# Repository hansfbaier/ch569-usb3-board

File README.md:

# CH569 USB3 Super Speed Board
USB3 super speed development board useful as FPGA expansion
based on the WCH-Tech CH569 chip.
It should also be possible to substitute the CH569 with a CH565 chip,
without further modifications.

### Board support
Open source development tools and board support package are available here:

https://github.com/orgs/hydrausb3/repositories

### Status
* rev0 tested and working
* rev1 tested and working
* rev2 tested and working. Passes stress test. Recommended!

NOTE: Both rev0 and rev1 have shown spurious transmission errors in USB3 stress tests.
Do not use for high performance duty. Adding a 100nF decoupling capacitor to the
3V3 pin of the crystal oscillator seemed to improve the situation significantly.

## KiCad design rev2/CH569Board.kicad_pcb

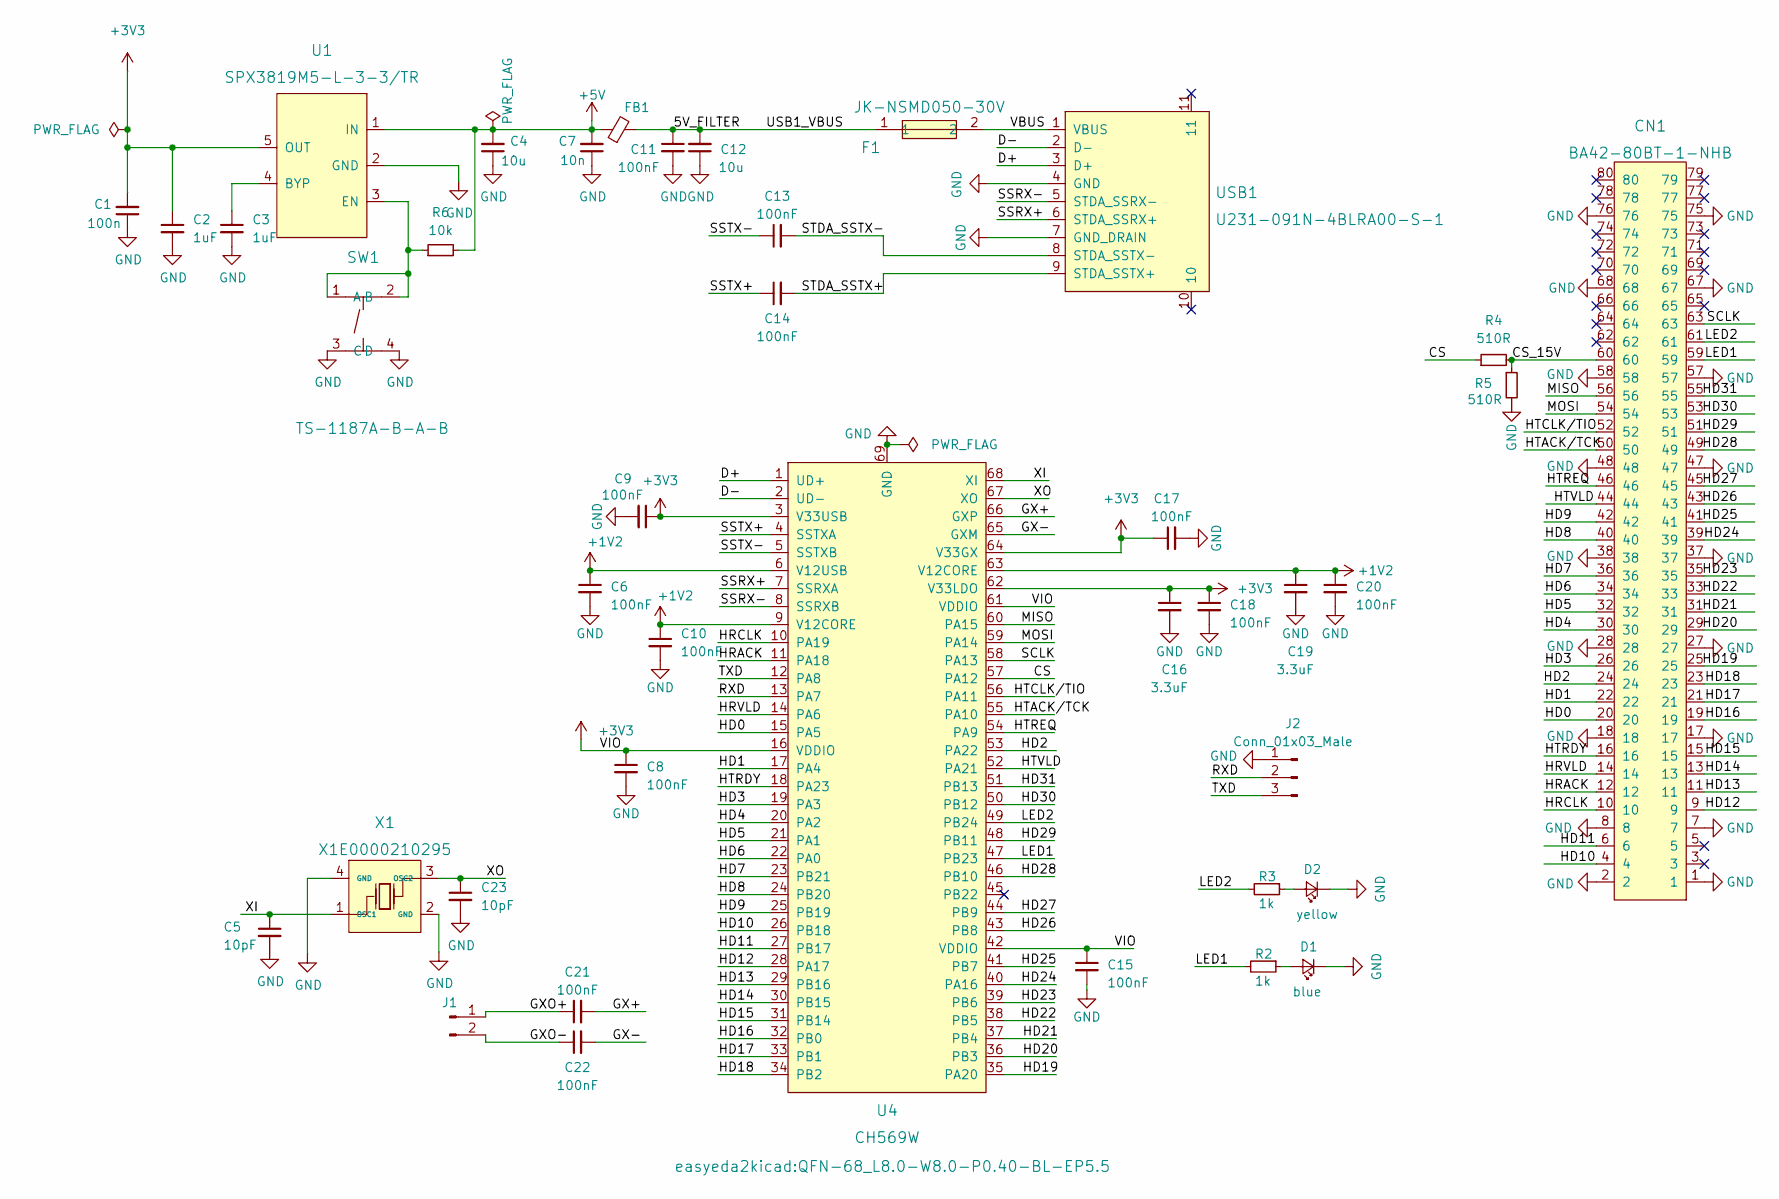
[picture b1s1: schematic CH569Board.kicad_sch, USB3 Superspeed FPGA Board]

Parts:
C1: 100n; C_0805_2012Metric; LCSC C49678
C2, C3: 1uF; C_0805_2012Metric; LCSC C28323
C4, C12: 10u; C_0805_2012Metric; LCSC C15850
C5, C23: 10pF; C_0402_1005Metric; LCSC C32949
C6, C8, C9, C10, C11, C17, C18, C20: 100nF; C_0805_2012Metric; LCSC C49678
C7: 10n; C_0805_2012Metric; LCSC C1710
C13, C14, C21, C22: 100nF; C_0402_1005Metric; LCSC C1525
C15: 100nF; C_0603_1608Metric; LCSC C14663
C16, C19: 3.3uF; C_0603_1608Metric; LCSC C51412
CN1: BA42-80BT-1-NHB; CONN-SMD_BA42-80BT-1-NHB; LCSC Part C508676
D1: blue; LED_0603_1608Metric; LCSC C72041
D2: yellow; LED_0603_1608Metric; LCSC C72038
F1: JK-NSMD050-30V; F1206; LCSC Part C720075
FB1: 2A; L_1206_3216Metric; LCSC C73732
J1: Conn_01x02_Male; PinHeader_1x02_P2.54mm_Vertical
J2: Conn_01x03_Male; PinHeader_1x03_P2.54mm_Vertical
R2, R3: 1k; R_0603_1608Metric; LCSC C21190
R4, R5: 510R; R_0402_1005Metric; LCSC C25123
R6: 10k; R_0402_1005Metric; LCSC C25744
SW1: TS-1187A-B-A-B; SW-SMD_4P-L5.1-W5.1-P3.70-LS6.5-TL-2; LCSC Part C318884
U1: SPX3819M5-L-3-3/TR; SOT-23-5_L3.0-W1.7-P0.95-LS2.8-BR; LCSC Part C9055
U4: CH569W; QFN-68_L8.0-W8.0-P0.40-BL-EP5.5; LCSC Part C2857462
USB1: U231-091N-4BLRA00-S-1; USB-A-SMD_U231-091N-4BLRA00-S-1; LCSC Part C381140
X1: X1E0000210295; CRYSTAL-SMD_4P-L3.2-W2.5-BL; LCSC Part C255930

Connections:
+1V2: C6.1, C10.1, C19.1, C20.1, U4.6 (V12USB), U4.9 (V12CORE), U4.63 (V12CORE)
+3V3: C1.2, C2.1, C8.1, C9.1, C15.1, C16.1, C17.1, C18.1, U1.5 (OUT), U4.3 (V33USB), U4.16 (VDDIO), U4.42 (VDDIO), U4.61 (VDDIO), U4.62 (V33LDO), U4.64 (V33GX)
+5V: C4.2, C7.2, FB1.1, R6.2, U1.1 (IN)
/5V_FILTER: C11.1, C12.2, F1.1, FB1.2
/CS: R4.1, U4.57 (PA12)
/CS_15V: CN1.60, R4.2, R5.1
/D+: U4.1 (UD+), USB1.3 (D+)
/D-: U4.2 (UD-), USB1.2 (D-)
/GX+: C21.2, U4.66 (GXP)
/GX-: C22.2, U4.65 (GXM)
/GXO+: C21.1, J1.1
/GXO-: C22.1, J1.2
/HD0: CN1.20, U4.15 (PA5)
/HD1: CN1.22, U4.17 (PA4)
/HD2: CN1.24, U4.53 (PA22)
/HD3: CN1.26, U4.19 (PA3)
/HD4: CN1.30, U4.20 (PA2)
/HD5: CN1.32, U4.21 (PA1)
/HD6: CN1.34, U4.22 (PA0)
/HD7: CN1.36, U4.23 (PB21)
/HD8: CN1.40, U4.24 (PB20)
/HD9: CN1.42, U4.25 (PB19)
/HD10: CN1.4, U4.26 (PB18)
/HD11: CN1.6, U4.27 (PB17)
/HD12: CN1.9, U4.28 (PA17)
/HD13: CN1.11, U4.29 (PB16)
/HD14: CN1.13, U4.30 (PB15)
/HD15: CN1.15, U4.31 (PB14)
/HD16: CN1.19, U4.32 (PB0)
/HD17: CN1.21, U4.33 (PB1)
/HD18: CN1.23, U4.34 (PB2)
/HD19: CN1.25, U4.35 (PA20)
/HD20: CN1.29, U4.36 (PB3)
/HD21: CN1.31, U4.37 (PB4)
/HD22: CN1.33, U4.38 (PB5)
/HD23: CN1.35, U4.39 (PB6)
/HD24: CN1.39, U4.40 (PA16)
/HD25: CN1.41, U4.41 (PB7)
/HD26: CN1.43, U4.43 (PB8)
/HD27: CN1.45, U4.44 (PB9)
/HD28: CN1.49, U4.46 (PB10)
/HD29: CN1.51, U4.48 (PB11)
/HD30: CN1.53, U4.50 (PB12)
/HD31: CN1.55, U4.51 (PB13)
/HRACK: CN1.12, U4.11 (PA18)
/HRCLK: CN1.10, U4.10 (PA19)
/HRVLD: CN1.14, U4.14 (PA6)
/HTACK/TCK: CN1.50, U4.55 (PA10)
/HTCLK/TIO: CN1.52, U4.56 (PA11)
/HTRDY: CN1.16, U4.18 (PA23)
/HTREQ: CN1.46, U4.54 (PA9)
/HTVLD: CN1.44, U4.52 (PA21)
/LED1: CN1.59, R2.2, U4.47 (PB23)
/LED2: CN1.61, R3.2, U4.49 (PB24)
/MISO: CN1.56, U4.60 (PA15)
/MOSI: CN1.54, U4.59 (PA14)
/RXD: J2.2, U4.13 (PA7)
/SCLK: CN1.63, U4.58 (PA13)
/SSRX+: U4.7 (SSRXA), USB1.6 (STDA_SSRX+)
/SSRX-: U4.8 (SSRXB), USB1.5 (STDA_SSRX-)
/SSTX+: C14.1, U4.4 (SSTXA)
/SSTX-: C13.1, U4.5 (SSTXB)
/STDA_SSTX+: C14.2, USB1.9 (STDA_SSTX+)
/STDA_SSTX-: C13.2, USB1.8 (STDA_SSTX-)
/TXD: J2.3, U4.12 (PA8)
/VBUS: F1.2, USB1.1 (VBUS)
/XI: C5.1, U4.68 (XI), X1.1 (OSC1)
/XO: C23.1, U4.67 (XO), X1.3 (OSC2)
GND: C1.1, C2.2, C3.2, C4.1, C5.2, C6.2, C7.1, C8.2, C9.2, C10.2, C11.2, C12.1, C15.2, C16.2, C17.2, C18.2, C19.2, C20.2, C23.2, CN1.1, CN1.2, CN1.7, CN1.8, CN1.17, CN1.18, CN1.27, CN1.28, CN1.37, CN1.38, CN1.47, CN1.48, CN1.57, CN1.58, CN1.67, CN1.68, CN1.75, CN1.76, D1.1 (K), D2.1 (K), J2.1, R5.2, SW1.3 (C), SW1.4 (D), U1.2 (GND), U4.69 (GND), USB1.4 (GND), USB1.7 (GND_DRAIN), X1.2 (GND), X1.4 (GND)
unnamed: C3.1, U1.4 (BYP)
unnamed: D1.2 (A), R2.1
unnamed: D2.2 (A), R3.1
unnamed: R6.1, SW1.1 (A), SW1.2 (B), U1.3 (EN)

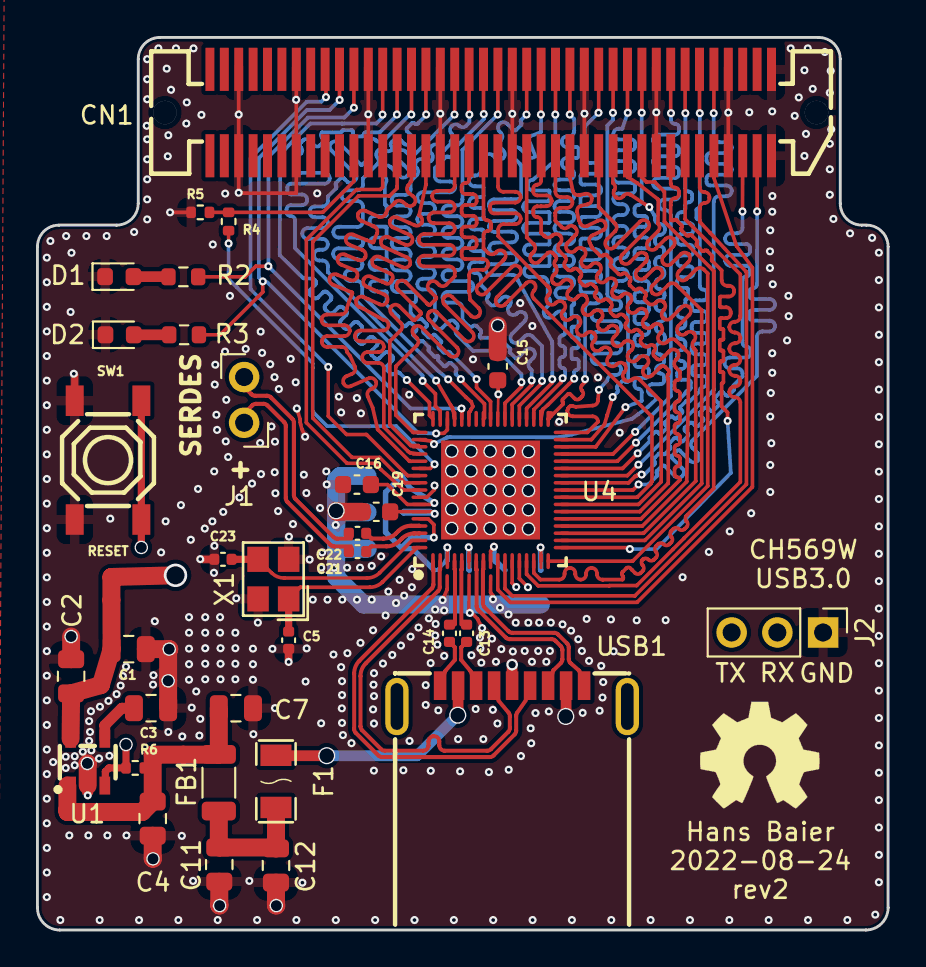
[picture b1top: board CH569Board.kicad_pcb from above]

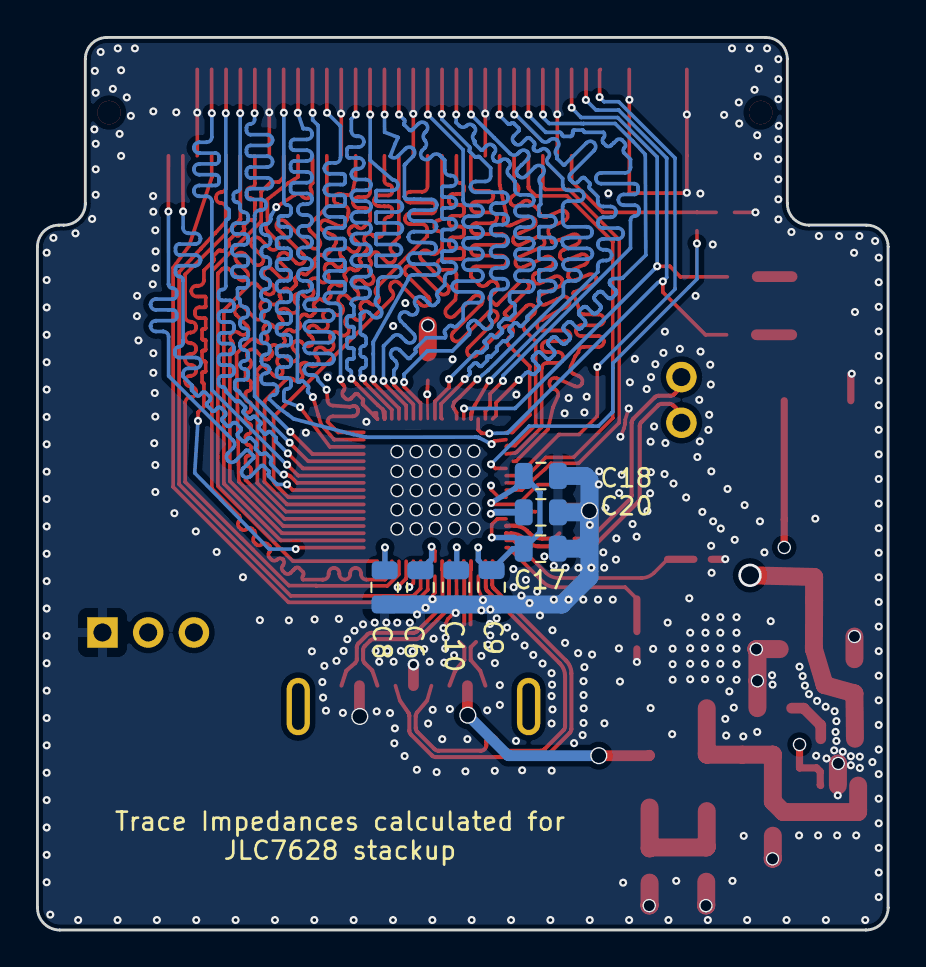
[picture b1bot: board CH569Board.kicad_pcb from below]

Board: 4 copper layers, 47.3 x 49.6 mm, 41 parts (7 on the bottom side), 73 nets.

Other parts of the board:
N1: OHWLOGO; OSHW-Symbol_6.7x6mm_SilkScreen

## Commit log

2022-04-09 Add LICENSE/README
2022-04-09 add schematic
2022-04-12 New Edge cuts from FreeCAD and match the board to FPGA main board
2022-04-12 update production files
2022-04-13 Big design fixup: Make Layer 3 a GND plane so signals reference ground. Eliminate one LED for better integrity of the signal traces, new board outline
2022-04-13 Update images in README
2022-04-18 Fix swapped pins 1 and 3 on the 1.2V regulator
2022-04-22 add decoupling caps in serdes, layout improvements
2022-04-22 move LEDs to a better place
2022-07-22 create rev0 subdirectory and move the first revision there
2022-07-23 board revision 1
2022-07-23 update README for rev1
2022-07-23 fix U2 silkscreen
2022-07-23 cosmetics
2022-07-23 export fixes to production files
2022-08-11 fix important flaw in rev1: 3.3V and VIO were not connected
2022-08-22 remove 1V2 regulator, create HSPI netclass, rewire 1V2 power net
2022-08-22 fix high speed tracks, move crystal closer, clean up power supply traces
2022-08-22 Some finishes. Put OSHW logo on silkscreen
2022-08-23 redo power section with different LDO, add decoupling cap and reset switch
2022-08-23 stitch board edges and add more ground vias
2022-08-23 rev2 ready for the fab. used a crystal instead of an XO, because of better specs
2022-08-23 move ground via closer to cap
2022-09-29 fix Pin64 short to ground and missing decoupling cap connection
